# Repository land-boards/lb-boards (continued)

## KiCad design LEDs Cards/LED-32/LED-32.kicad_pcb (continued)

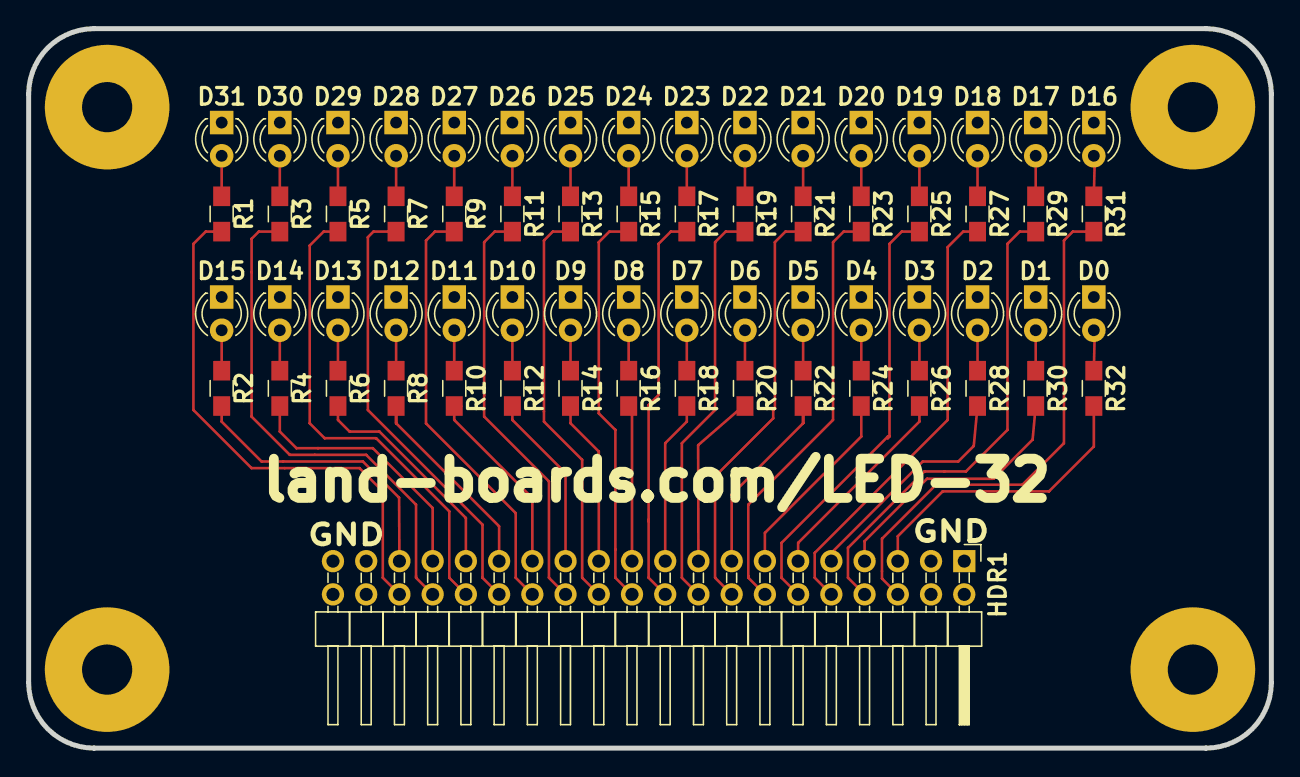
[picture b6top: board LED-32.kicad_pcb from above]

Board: 2 copper layers, 95.0 x 55.0 mm, 70 parts (0 on the bottom side), 65 nets.

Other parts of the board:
TEST: COUPON; TEST_BLK-REAR
